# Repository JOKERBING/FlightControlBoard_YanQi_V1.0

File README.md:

# YanQi Flight Control Board V1.0

配合NxtPX4飞控板使用的一款扩展板。

<div align=center></div>

## Physical

- Mounting: 79 x 42 mm, Φ 3 mm  20 x 20 mm, Φ 3 mm
- Dimensions: 87.5 x 97.5 x 8 mm
- Weight: 20 g

## Specifications

- ESC: 4 x Bluejay
- 10 x SRGBLED neopixel
- 2 x ADC (Battery Voltage, Current)
- 1 x GPS

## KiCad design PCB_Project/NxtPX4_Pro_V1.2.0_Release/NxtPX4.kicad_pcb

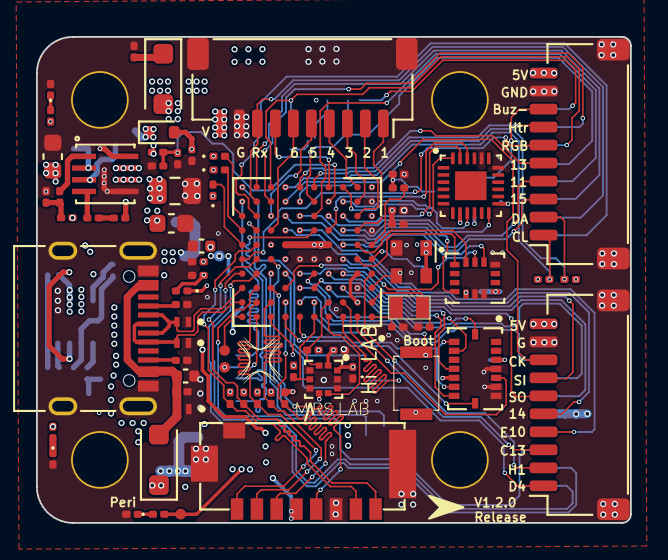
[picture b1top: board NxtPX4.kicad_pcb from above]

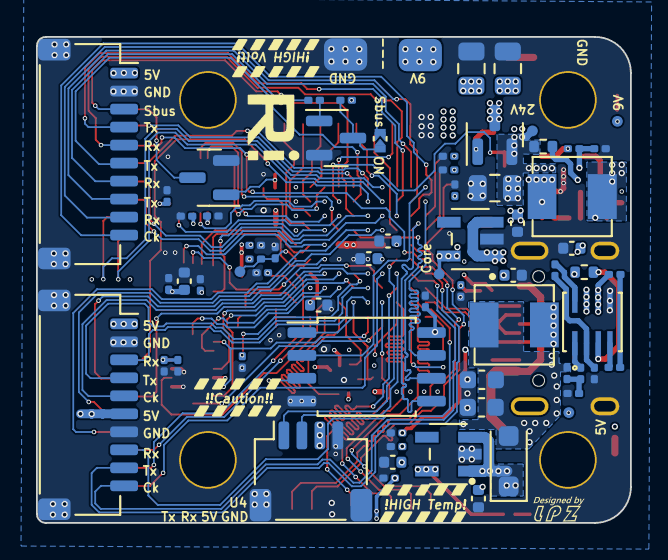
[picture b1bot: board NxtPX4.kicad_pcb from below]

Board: 4 copper layers, 33.0 x 27.0 mm, 151 parts (73 on the bottom side), 127 nets.

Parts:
BOOT1: TD-1183SN-1.5H(3x2.5); 3x2.5PushButton
C1, C3, C12, C13: 22uF(0805 35V 20%); C_0805_2012Metric
C2: 10uF(0603 35V 20%); C_0603_1608Metric
C4, C8: 1uF(0402 35V 10%); C_0402_1005Metric
C5, C6, C9: 1uF(0402 16V 10%); C_0402_1005Metric
C7, C10, C16, C18, C19, C20, C33, C34, C37, C38, C39, C42, C48, C51: 100nF(0201 10V 10%); C_0201_0603Metric
C11: 100nF(0201 16V 10%); C_0201_0603Metric
C14, C15: 1uF(0402 10V 10%); C_0402_1005Metric
C17, C21: 100nF(0201 25V 10%); C_0201_0603Metric
C22: 100nF(0201 10.0V 10%); C_0201_0603Metric
C23, C24, C26: 22uF(0603 16V); C_0603_1608Metric
C27, C28, C50: 2.2uF(0402 6.3V 10%); C_0402_1005Metric
C29: 4.7uF(0402 10V); C_0402_1005Metric
C30: 15pF(0201 10V); C_0201_0603Metric
C31: 100nF(0201 6.3V); C_0201_0603Metric
C32: 1uF(0201 6.3V); C_0201_0603Metric
C35, C36: 12.0pF(0201 10V); C_0201_0603Metric
C44, C47: 100.0nF(0201 10V); C_0201_0603Metric
C45, C49: 100nF(0201 10V); C_0201_0603Metric
C52: 10nF(0201 10V 10%); C_0201_0603Metric
D1: PESD12VV1BL; PESD12VV1BL_315
D2, D4: PESD5V0F1BL
D3: SMF30CA(30V); D_SOD-123F
D5, D7: DSS34(3A 500mV); D_SOD-123F
D6: BZX584C9V1; D_SOD-523
D8, D9, D10, D11: LED_Blue(0201); LED_0201_0603Metric
D12: LED_RED(0201); LED_0201_0603Metric
D13: LED_BLUE(0201); LED_0201_0603Metric
D14: LED_Green(0201); LED_0201_0603Metric
H1, H2, H3, H4: MountingHole_Pad; M2MountingHole
J1: USB_C_Receptacle_USB2.0; USB_C_Small
J3: 9V_Power; Conn_1pin_Power
J4, J6, J10: ESC; 01x10_MP_sh1.0_Hori
J8: UART_Combo; 01x10_MP_sh1.0_Hori
J9: Upper computer connector; 01x04_MP_sh1.0_Hori
J24: Micro_SD_Card; TF-SMD_TF-021B-H265
J27: GND; Conn_1pin_Power
L1, L2: 10uH(0420)(78438357100); Inductor_0420
Q1: AP40P05; SOT-23
Q2, Q3: SS8050(NPN BEC); SOT-23
R1, R2: 5.1kR(0201); R_0201_0603Metric
R3, R8: 100kR(0201 50V); R_0201_0603Metric
R4, R6: 1MR(0402 50V); R_0402_1005Metric
R5, R7: 100kR(0201 25V); R_0201_0603Metric
R9, R11: 20R(0201 25V); R_0201_0603Metric
R10, R13: 51kR(0201 25V); R_0201_0603Metric
R12: 7.68kR(0201 25V); R_0201_0603Metric
R14, R18: 41.2kR(0201 25V); R_0201_0603Metric
R15: 200.0kR(0201 50V); R_0201_0603Metric
R16: 22.0kR(0201 50V); R_0201_0603Metric
R17: 3.54k-4.02kR(0201 25V); R_0201_0603Metric
R19, R20, R21, R26, R30, R31, R37, R38, R39, R40, R41: 10kR(0201); R_0201_0603Metric
R22: 20kR(0201 9V); R_0201_0603Metric
R23, R29: 1kR(0201); R_0201_0603Metric
R24, R25: 4.7kR(0201 25V); R_0201_0603Metric
R28: 100R(0201); R_0201_0603Metric
R32, R33, R34: 10.0kR(0201); R_0201_0603Metric
R35, R36: 4.7kR(0201); R_0201_0603Metric
TP1: 24V_TP; MiniTP
TP2: 3.3V_Core_TP; MiniTP
TP5: 3.3V_Peri_TP; MiniTP
TP9: 5V_System; MiniTP
TP12: CAM_9V; MiniTP
TP14, TP15, TP16: TP; MiniTP
U1, U4: MP9943GQ-Z
U2, U3: RT9013-33GB
U5: HKU_Logo
U6: UAV_LOGO; Uav_logo
U7: Direction_Logo
U8: RI_LOGO; Ri_logo
U9: STM32H743VIH6; STM32H743VIHBGA100C80P10X10_800X800X110N
U10: BMI088
U12: HiLAB_Logo; HILAB_Logo
U13: BMP388; PQFN50P200X200X80-10N
U14: W25Q128JVS; SOIC-8_5.23x5.23mm_P1.27mm
U15: Signature; my_signature
U16: High_temp; high_temp
U17: high_voltage
U18: Caution
U20: handsolder_connect
U21: ICM-20649
U22: ICM-42688-P
USART_Combo1: UART_Combo; 01x10_MP_sh1.0_Hori
Y1: SG-210STF/ X1G004171002700; Oscillator_SMD_Abracon_ASDMB-4Pin_2.5x2.0mm
Y2: ABS07 (32.768kHZ); LSE(2012)

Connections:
/AUX_PC0: R28.2, U9.F1 (PC0)
/AUX_PC13: J6.3, U9.A2 (PC13)
/AUX_PD4: J6.1, U9.D7 (PD4)
/AUX_PH1: J6.2, U9.D1 (PH1-OSC_OUT)
/BAT_I: J10.7, U9.K4 (PB1)
/BAT_V: C22.1, R15.2, R16.1, U9.J4 (PB0)
/BMI_Accel_CS: U9.C3 (PE4), U10.14 (CSB1)
/BMI_Accel_Data_RDY: U9.C4 (PE1), U10.16 (INT1)
/BMI_Gryo_CS: U9.B3 (PE3), U10.5 (CSB2)
/BMI_Gyro_Data_RDY: U9.D4 (PE0), U10.12 (INT3)
/BMP_Data_RDY: U9.A4 (PB9), U13.7 (INT)
/Buzzer-: J4.8, Q3.3 (C)
/Buzzer_RGB_LED: J4.6, U9.E10 (PC7)
/Extern_I2C_INT_PE15: J4.3, U9.H7 (PE15)
/Extern_IMU_Heater: J4.7, U9.K5 (PE9)
/Extern_SPI_CS_1_PE13: J4.5, U9.K6 (PE13)
/Extern_SPI_CS_2_PE14: J6.5, U9.G7 (PE14)
/Extern_SPI_INT_1_PE10: J6.4, U9.G6 (PE10)
/Extern_SPI_INT_2_PE11: J4.4, U9.H6 (PE11)
/I2C1_SCL: R36.2, U9.B4 (PB8), U13.2 (SCK)
/I2C1_SDA: R35.2, U9.A5 (PB7), U13.4 (SDI)
/I2C2_SCL: J4.1, R24.1, U9.J7 (PB10)
/I2C2_SDA: J4.2, R25.1, U9.K7 (PB11)
/ICM_Data_RDY: U9.G3 (PA4), U22.4 (INT1/INT)
/ICM_~CS: U9.F3 (PC3_C), U22.12 (AP_CS)
/LED_BLUE: D13.2 (A), U9.G10 (PB15)
/LED_GREEN: D14.2 (A), U9.H10 (PB14)
/LED_RED: D12.2 (A), U9.F10 (PC6)
/MPU_Data_RDY: U9.H4 (PC5), U21.12 (INT1)
/MPU_~CS: U9.G4 (PC4), U21.22 (~CS)
/NRST: C33.1, R30.2, TP14.1, U9.E1 (NRST)
/PWM/DSHOT_CH1: J10.1, U9.G2 (PA0)
/PWM/DSHOT_CH2: J10.2, U9.H2 (PA1)
/PWM/DSHOT_CH3: J10.3, U9.J2 (PA2)
/PWM/DSHOT_CH4: J10.4, U9.K2 (PA3)
/PWM/DSHOT_CH5: J10.5, U9.H8 (PD14)
/PWM/DSHOT_CH6: J10.6, U9.G8 (PD15)
/QSPI_BK1_IO0: U9.G9 (PD11), U14.5 (DI(IO0))
/QSPI_BK1_IO1: U9.K10 (PD12), U14.2 (DO(IO1))
/QSPI_BK1_IO2: U9.A3 (PE2), U14.3 (IO2)
/QSPI_BK1_IO3: U9.J10 (PD13), U14.7 (IO3)
/QSPI_BK1_~CS: U9.B5 (PB6), U14.1 (~CS)
/QSPI_CLK: U9.G5 (PB2), U14.6 (CLK)
/SBUS: J8.3, R23.2
/SCLK: TP16.1, U9.A9 (PA14)
/SDMMC1_CK: J24.5 (CLK), U9.C8 (PC12)
/SDMMC1_CMD: J24.3 (CMD), R39.1, U9.B7 (PD2)
/SDMMC1_D0: J24.7 (DAT0), R40.1, U9.F9 (PC8)
/SDMMC1_D1: J24.8 (DAT1), R41.1, U9.E9 (PC9)
/SDMMC1_D2: J24.1 (DAT2), R37.1, U9.B9 (PC10)
/SDMMC1_D3: J24.2 (DAT3/CD), R38.1, U9.B8 (PC11)
/SPI1_MISO: U9.J3 (PA6), U21.9 (SDO)
/SPI1_MOSI: U9.K3 (PA7), U21.24 (SDI)
/SPI1_SCK: U9.H3 (PA5), U21.23 (SCLK)
/SPI2_MISO: U9.E2 (PC2_C), U22.1 (AP_SDO/AP_AD0)
/SPI2_MOSI: U9.F2 (PC1), U22.14 (AP_SDA/AP_SDIO/AP_SDI)
/SPI2_SCK: U9.C7 (PD3), U22.13 (AP_SCL/AP_SCLK)
/SPI3_MISO: U9.A6 (PB4), U10.10 (SDO2), U10.15 (SDO1)
/SPI3_MOSI: U9.C5 (PB5), U10.9 (SDI)
/SPI3_SCK: U9.A7 (PB3), U10.8 (SCK)
/SPI4_MISO: J6.6, U9.D3 (PE5)
/SPI4_MOSI: J6.7, U9.E3 (PE6)
/SPI4_SCK: J6.8, U9.J6 (PE12)
/SWDIO: TP15.1, U9.A10 (PA13)
/UART4_RX: J9.2, U9.D8 (PD0)
/UART4_TX: J9.1, U9.E8 (PD1)
/UART5_RX: J8.5, U9.K8 (PB12), U20.2 (NC)
/UART5_TX: J8.4, U9.J8 (PB13)
/UART7_RX: J8.7, U9.H5 (PE7)
/UART7_TX: J8.6, U9.J5 (PE8)
/USART1_CK: U9.D9 (PA8), USART_Combo1.10
/USART1_RX: U9.D10 (PA10), USART_Combo1.9
/USART1_TX: U9.C9 (PA9), USART_Combo1.8
/USART2_CK: U9.D6 (PD7), USART_Combo1.5
/USART2_RX: U9.C6 (PD6), USART_Combo1.4
/USART2_TX: U9.B6 (PD5), USART_Combo1.3
/USART3_CK: J8.10, U9.H9 (PD10)
/USART3_RX: J8.9, J10.8, U9.J9 (PD9)
/USART3_TX: J8.8, U9.K9 (PD8)
/USB_OTG_FS_DM: D2.2 (A2), J1.A7 (D-), J1.B7 (D-), U9.C10 (PA11)
/USB_OTG_FS_DP: D4.2 (A2), J1.A6 (D+), J1.B6 (D+), U9.B10 (PA12)
/VBUS: C9.1, C11.1, D1.2 (A2), D5.2 (A), J1.A4 (VBUS), J1.A9 (VBUS), J1.B4 (VBUS), J1.B9 (VBUS)
CAM_9V: C26.1, D11.2 (A), J3.1, L2.2, R18.2, TP12.1
Core_3V3: BOOT1.1, C14.1, C16.1, C19.1, C29.2, C31.1, C32.1, C34.1, C39.2, C44.1, C45.2, C47.1, C48.2, C49.1, C50.2, C51.2, C52.1, D8.2 (A), R24.2, R25.2, R26.1, R30.1, R35.1, R36.1, R37.2, R38.2, R39.2, R40.2, R41.2, TP2.1, U2.5 (VOUT), U9.A8 (PA15), U9.B2 (VBAT), U9.D2 (VDD), U9.F4 (VDDLDO), U9.F5 (VDD), U9.F6 (VDD33USB), U9.F7 (PDR_ON), U9.H1 (VDDA), U9.K1 (VDD), U10.3 (VDD), U10.11 (VDDIO), U13.1 (VDDIO), U13.6 (CSB), U13.10 (VDD), U21.8 (VDDIO), U21.13 (VDD), U22.5 (VDDIO), U22.8 (VDD), Y1.1 (~ST), Y1.4 (VCC)
GND: C1.2, C2.2, C3.2, C4.2, C5.2, C6.2, C7.2, C8.2, C9.2, C10.2, C11.2, C12.2, C13.2, C14.2, C15.2, C16.2, C18.2, C19.2, C20.2, C22.2, C23.2, C24.2, C26.2, C27.1, C28.1, C29.1, C30.2, C31.2, C32.2, C33.2, C34.2, C35.2, C36.2, C37.2, C38.2, C39.1, C42.2, C44.2, C45.1, C47.2, C48.1, C49.2, C50.1, C51.1, C52.2, D1.1 (A1), D2.1 (A1), D4.1 (A1), H1.1, H2.1, H3.1, H4.1, J1.A1 (GND), J1.A12 (GND), J1.B1 (GND), J1.B12 (GND), J1.S1 (SHIELD), J4.9, J4.MP (MountPin), J6.9, J6.MP (MountPin), J8.2, J8.MP (MountPin), J9.4, J9.MP (MountPin), J10.9, J10.MP (MountPin), J24.6 (VSS), J24.9 (SHIELD), J27.1, Q2.2 (E), Q3.2 (E), R1.1, R2.1, R3.2, R8.2, R12.1, R16.2, R17.1, R19.1, R20.1, R21.1, R22.1, R29.1, R31.1, R32.2, R33.2, R34.2, U1.5 (GND), U2.2 (GND), U3.2 (GND), U4.5 (GND), U9.C2 (VSS), U9.E4 (VSS), U9.E5 (VSS), U9.E6 (VSS), U9.G1 (VSSA), U9.J1 (VSS), U10.4 (GNDIO), U10.6 (GND), U10.7 (PS), U13.3 (VSS), U13.5 (SDO), U13.8 (VSS), U13.9 (VSS), U14.4 (GND), U21.18 (GND), U21.20 (RESV), U22.6 (GND), U22.7 (RESV), U22.11 (RESV), USART_Combo1.2, USART_Combo1.7, USART_Combo1.MP (MountPin), Y1.2 (GND)
unnamed: C27.2, U9.E7 (VCAP)
unnamed: C28.2, U9.F8 (VCAP)
unnamed: C17.1, R9.2
unnamed: C21.1, R11.2
unnamed: D3.1 (A1), R3.1
unnamed: D6.2 (A), Q1.1 (G), R8.1
unnamed: D8.1 (K), R19.2
unnamed: D9.1 (K), R20.2
unnamed: D10.1 (K), R21.2
unnamed: D11.1 (K), R22.2
unnamed: D12.1 (K), R32.1
unnamed: D13.1 (K), R33.1
unnamed: D14.1 (K), R34.1
unnamed: J1.A5 (CC1), R2.2
unnamed: J1.B5 (CC2), R1.2
unnamed: Q2.1 (B), R23.1
unnamed: Q2.3 (C), R26.2, U20.1 (NC)
unnamed: Q3.1 (B), R28.1, R29.2
unnamed: R10.2, R12.2, R14.1
unnamed: R13.2, R17.2, R18.1
unnamed: R9.1, U1.4 (BST)
unnamed: R4.2, U1.3 (EN/SYNC)
unnamed: R10.1, U1.1 (FB)
unnamed: R5.2, U1.8 (PG)
unnamed: C17.2, L1.1, U1.6 (SW)
unnamed: C7.1, R5.1, U1.2 (VCC)
unnamed: R11.1, U4.4 (BST)
unnamed: R6.2, U4.3 (EN/SYNC)
unnamed: R13.1, U4.1 (FB)
unnamed: R7.2, U4.8 (PG)
unnamed: C21.2, L2.1, U4.6 (SW)
unnamed: C10.1, R7.1, U4.2 (VCC)
unnamed: C35.1, U9.A1 (PC14-OSC32_IN), Y2.2
unnamed: C36.1, U9.B1 (PC15-OSC32_OUT), Y2.1
unnamed: BOOT1.2, R31.2, U9.D5 (BOOT0)
unnamed: C30.1, U9.C1 (PH0-OSC_IN), Y1.3 (OUT)
unnamed: C42.1, U21.10 (REGOUT)
Periph_3V3: C15.1, C18.1, C20.1, C37.1, C38.1, D9.2 (A), J24.4 (VDD), TP5.1, U3.5 (VOUT), U14.8 (VCC)
System_4V5: C5.1, C6.1, D5.1 (K), D7.1 (K), U2.1 (VIN), U2.3 (EN), U3.1 (VIN), U3.3 (EN)
System_5V: C23.1, C24.1, D7.2 (A), D10.2 (A), J4.10, J6.10, J8.1, J9.3, L1.2, R14.2, TP9.1, USART_Combo1.1, USART_Combo1.6
VCC_24V: C1.1, C2.1, C3.1, C4.1, C8.1, D6.1 (K), Q1.2 (S), R4.1, R6.1, R15.1, TP1.1, U1.7 (IN), U4.7 (IN)
VCC_BAT: C12.1, C13.1, D3.2 (A2), J10.10, Q1.3 (D)

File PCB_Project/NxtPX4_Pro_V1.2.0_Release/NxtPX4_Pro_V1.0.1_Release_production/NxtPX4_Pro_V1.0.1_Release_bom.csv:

Designator,Footprint,Quantity,Value,LCSC Part #
BOOT1,3x2.5PushButton,1,TD-1183SN-1.5H(3x2.5),
C1,0805,1,22uF(0805 35V 20%),
C10,0201,1,100nF(0201 10V 10%),
C11,0201,1,100nF(0201 16V 10%),
C12,0805,1,22uF(0805 35V 20%),
C13,0805,1,22uF(0805 35V 20%),
C14,0402,1,1uF(0402 10V 10%),
C15,0402,1,1uF(0402 10V 10%),
C16,0201,1,100nF(0201 10V 10%),
C17,0201,1,100nF(0201 25V 10%),
C18,0201,1,100nF(0201 10V 10%),
C19,0201,1,100nF(0201 10V 10%),
C2,0603,1,10uF(0603 35V 20%),
C20,0201,1,100nF(0201 10V 10%),
C21,0201,1,100nF(0201 25V 10%),
C22,0201,1,100nF(0201 10.0V 10%),
C23,0603,1,22uF(0603 16V),
C24,0603,1,22uF(0603 16V),
C26,0603,1,22uF(0603 16V),
C27,0402,1,2.2uF(0402 6.3V 10%),
C28,0402,1,2.2uF(0402 6.3V 10%),
C29,0402,1,4.7uF(0402 10V),
C3,0805,1,22uF(0805 35V 20%),
C30,0201,1,15pF(0201 10V),
C31,0201,1,100nF(0201 6.3V),
C32,0201,1,1uF(0201 6.3V),
C33,0201,1,100nF(0201 10V 10%),
C34,0201,1,100nF(0201 10V 10%),
C35,0201,1,12.0pF(0201 10V),
C36,0201,1,12.0pF(0201 10V),
C37,0201,1,100nF(0201 10V 10%),
C38,0201,1,100nF(0201 10V 10%),
C39,0201,1,10nF(0201 10V 10%),
C4,0402,1,1uF(0402 35V 10%),
C40,0201,1,100nF(0201 10V 10%),
C41,0201,1,2.2uF(0201 10V 10%),
C42,0201,1,100nF(0201 10V 10%),
C43,0201,1,10nF(0201 10V 10%),
C44,0201,1,100.0nF(0201 10V),
C45,0201,1,100nF(0201 10V),
C46,0201,1,100nF(0201 10V),
C47,0201,1,100.0nF(0201 10V),
C48,0201,1,100nF(0201 10V 10%),
C49,0201,1,100nF(0201 10V),
C5,0402,1,1uF(0402 16V 10%),
C6,0402,1,1uF(0402 16V 10%),
C7,0201,1,100nF(0201 10V 10%),
C8,0402,1,1uF(0402 35V 10%),
C9,0402,1,1uF(0402 16V 10%),
D1,PESD12VV1BL_315,1,PESD12VV1BL,
D10,0201,1,LED_Blue(0201),
D11,0201,1,LED_Blue(0201),
D12,0201,1,LED_RED(0201),
D13,0201,1,LED_BLUE(0201),
D14,0201,1,LED_Green(0201),
"D2, D4",PESD5V0F1BL,2,PESD5V0F1BL,
D3,D_SOD-123F,1, SMF30CA(30V),
"D5, D7",D_SOD-123F,2,DSS34(3A 500mV),
D6,D_SOD-523,1,BZX584C9V1,
D8,0201,1,LED_Blue(0201),
D9,0201,1,LED_Blue(0201),
J1,USB_C_Small,1,USB_C_Receptacle_USB2.0,
J10,01x10_MP_sh1.0_Hori,1,ESC,
J24,TF-SMD_TF-021B-H265,1,Micro_SD_Card,
J9,01x04_sh1.0,1,Upper computer connector,
"L1, L2",Inductor_0420,2,10uH(0420),
Q1,SOT-23,1,AP40P05,
"Q2, Q3",SOT-23,2,SS8050(NPN BEC),
R1,0201,1,5.1kR(0201),
R10,0201,1,51kR(0201 25V),
R11,0201,1,20R(0201 25V),
R12,0201,1,7.68kR(0201 25V),
R13,0201,1,51kR(0201 25V),
R14,0201,1,41.2kR(0201 25V),
R15,0201,1,200.0kR(0201 50V),
R16,0201,1,22.0kR(0201 50V),
R17,0201,1,3.54k-4.02kR(0201 25V),
R18,0201,1,41.2kR(0201 25V),
R19,0201,1,10kR(0201),
R2,0201,1,5.1kR(0201),
R20,0201,1,10kR(0201),
R21,0201,1,10kR(0201),
R22,0201,1,20kR(0201 9V),
R23,0201,1,1kR(0201),
R24,0201,1,4.7kR(0201 25V),
R25,0201,1,4.7kR(0201 25V),
R26,0201,1,10kR(0201),
R28,0201,1,100R(0201),
R29,0201,1,1kR(0201),
R3,0201,1,100kR(0201 50V),
R30,0201,1,10kR(0201),
R31,0201,1,10kR(0201),
R32,0201,1,10.0kR(0201),
R33,0201,1,10.0kR(0201),
R34,0201,1,10.0kR(0201),
R35,0201,1,4.7kR(0201),
R36,0201,1,4.7kR(0201),
R37,0201,1,10kR(0201),
R38,0201,1,10kR(0201),
R39,0201,1,10kR(0201),
R4,0402,1,1MR(0402 50V),
R40,0201,1,10kR(0201),
R41,0201,1,10kR(0201),
R5,0201,1,100kR(0201 25V),
R6,0402,1,1MR(0402 50V),
R7,0201,1,100kR(0201 25V),
R8,0201,1,100kR(0201 50V),
R9,0201,1,20R(0201 25V),
"U1, U4",MP9943GQ-Z,2,MP9943GQ-Z,
U10,BMI088,1,BMI088,
U11,ICM-20602,1,ICM-20602,
U12,MPU-6500,1,MPU6500,
U13,PQFN50P200X200X80-10N,1,BMP388,
U14,SOIC-8_5.23x5.23mm_P1.27mm,1,W25Q128JVS,
"U2, U3",RT9013-33GB,2,RT9013-33GB,
U9,STM32H743VIHBGA100C80P10X10_800X800X110N,1,STM32H743VIH6,
Y1,Oscillator_SMD_Abracon_ASDMB-4Pin_2.5x2.0mm,1,SG-210STF/ X1G004171002700,
Y2,LSE(2012),1,ABS07 (32.768kHZ),

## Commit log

2023-08-22 删除文件 PCB_Project/YanXi_Project.eprj
2023-08-22 删除文件 PCB_Project/0819f05c4eef4c71ace90d822a990e87
2023-08-22 删除文件 PCB_Project
2025-03-10 add LICENSE.
2025-03-10 add files

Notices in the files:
parts and their libraries:
Copyright 2021 Accelerated Designs. All rights reserved.
